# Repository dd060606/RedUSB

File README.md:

# RedUSB

RedUSB is a DIY USB macro device: a custom PCB built around an **Adafruit KB2040 (RP2040)** that acts as a programmable USB HID keyboard. You write simple scripts in a Ducky-Script–style language, drop them onto the device like a USB stick, and play them back as real keystrokes.

A single physical switch flips the device between two personalities:

- **Config mode** : the device appears as a USB flash drive. Copy your `.txt` scripts onto it.
- **Attack mode** : the device appears as a USB keyboard. The selected script runs automatically on connect (or on a button press).

The firmware is written in Rust (`no_std`) and runs bare-metal on the RP2040.

---

## Features

- **Ducky-Script–style language** : `STRING`, `DELAY`, `REPEAT`, key combos (`GUI r`, `CTRL ALT t`, ...), and more.
- **Up to 16 scripts on the device**, selectable with the button; an RGB LED shows which one is active.
- **Auto-run on connect** : in attack mode the selected script fires once the host is ready.
- **US / French (AZERTY) keyboard layouts**, switchable per script with `LAYOUT`.
- **Conditional execution** per host OS with `IF_OS` / `ELSE` / `END_IF` (best-effort detection).
- **Firmware updates over USB** (UF2), no external programmer required.

---

## How it works

The **mode switch** (GPIO8) selects the personality at power-up:

| Switch       | Mode       | USB device                    | Button does               |
| ------------ | ---------- | ----------------------------- | ------------------------- |
| To GND (low) | **Config** | Mass storage (`REDUSB` drive) | Cycle the selected script |
| Open (high)  | **Attack** | HID keyboard                  | Run the selected script   |

Flipping the switch while plugged in reboots the device into the other mode.

### Config mode

The device mounts as a FAT drive named `REDUSB`. Copy script files (`.txt`) onto it. Each button press selects the next script, and the LED shows its slot color so you know which one is armed. The selection is saved to flash and survives power cycles.

### Attack mode

The device enumerates as a USB keyboard. About a second after the host finishes setting it up, the **selected script runs automatically**. You can also press the button at any time to re-run it.

> **Safety:** because the script auto-runs on connect, make sure the right script is selected and the intended window is focused before you plug into attack mode. Only use this on machines you are authorized to test.

---

## Hardware

- **MCU board:** Adafruit KB2040 (RP2040, 8 MB QSPI flash)
- **Push button** on GPIO5 (active-low, to GND)
- **Mode switch** on GPIO8 (active-low, to GND)
- **RGB LED** (common anode, active-low): blue = GPIO2, red = GPIO3, green = GPIO4
- **USB-A** connector and a 500 mA resettable fuse on the PCB

KiCad sources, the 3D model, and production/assembly files live in `PCB/` and `3D/`.

---

## Repository layout

```
RedUSB/
├── 3D/            Mechanical / enclosure model
├── PCB/           KiCad project and fabrication files
├── Firmware/      Rust firmware (Cargo workspace)
│   ├── core/      Hardware-independent logic: FAT, Ducky engine, layouts (host-tested)
│   └── firmware/  RP2040 binary: USB, flash storage, LED, button, modes
├── scripts/       Ready-to-run test / example scripts
└── README.md
```

---

## Building and flashing

### Prerequisites

Install the [Rust toolchain](https://rustup.rs/) (the correct target is pinned by `rust-toolchain.toml`), then the two build/flash helpers:

```bash
cargo install flip-link      # linker used by the firmware
cargo install elf2uf2-rs     # builds the UF2 and copies it to the board
```

All firmware commands below are run from the `Firmware/firmware/` directory.

### Flashing

`cargo run --release` builds **and** flashes in a single step : the project's Cargo runner converts the firmware to a `.uf2` and copies it to the board, so there's no separate build command to remember.

1. Put the board into bootloader mode. It should appear as the `RPI-RP2` drive:
    - **First flash (blank board):** hold the **BOOT button on the KB2040 itself** while plugging in the USB cable.
    - **Updating an already-flashed board:** set the mode switch to **Config**, hold the **PCB button (GPIO5)**, then plug in : the firmware reboots straight into the bootloader.
2. Flash it:
    ```bash
    cargo run --release
    ```
    The board reboots into the new firmware when it finishes.

> To just compile without flashing (for example to check it builds), use `cargo build --release`.

---

## Writing and running scripts

Scripts are plain `.txt` files placed in the root of the `REDUSB` drive (config mode). Filenames follow the FAT **8.3** convention (up to 8 characters before the extension), and scripts are sorted by name, so prefixes like `1_`, `2_` give a predictable order. Up to 16 scripts are tracked.

See the [`scripts/`](scripts/) folder for ready-to-run examples that exercise every feature.

### Workflow

1. Set the switch to **Config** and plug in. The `REDUSB` drive appears.
2. Copy your `.txt` script(s) onto it.
3. Press the button to select a script (the LED color tells you which : see below).
4. Focus the target window, then set the switch to **Attack** and plug in. The selected script runs automatically (or press the button).

### Script language

| Command                     | Example                              | Meaning                                                        |
| --------------------------- | ------------------------------------ | -------------------------------------------------------------- |
| `REM`                       | `REM a comment`                      | Comment, ignored                                               |
| `STRING`                    | `STRING hello`                       | Type text (no newline)                                         |
| `STRINGLN`                  | `STRINGLN hello`                     | Type text, then Enter                                          |
| `DELAY`                     | `DELAY 500`                          | Wait 500 ms                                                    |
| `DEFAULT_DELAY`             | `DEFAULT_DELAY 50`                   | Pause after every command                                      |
| `REPEAT`                    | `REPEAT 3`                           | Repeat the previous command 3 more times                       |
| `LAYOUT`                    | `LAYOUT FR`                          | Keyboard layout for `STRING` (`US` or `FR`)                    |
| Key / combo                 | `GUI r`, `CTRL ALT t`, `ENTER`, `F5` | Press a key, optionally with modifiers                         |
| `IF_OS` … `ELSE` … `END_IF` | `IF_OS WINDOWS`                      | Run a block only on a given OS                                 |
| `OS_REPORT`                 | `OS_REPORT`                          | Type the detected OS and USB enumeration counters (diagnostic) |

Modifiers: `CTRL`, `SHIFT`, `ALT`, `GUI`/`WINDOWS`, `ALTGR`. The default layout is French (AZERTY).

---

## LED reference

**Config mode : selected script slot:**

| Slot  | 0   | 1     | 2    | 3      | 4    | 5       | 6     | 7      |
| ----- | --- | ----- | ---- | ------ | ---- | ------- | ----- | ------ |
| Color | Red | Green | Blue | Yellow | Cyan | Magenta | White | Orange |

(Slots 8–15 use the same colors, blinking. A slow white "breathing" glow means no scripts are present.)

**Attack mode:**

| LED                     | Meaning                                        |
| ----------------------- | ---------------------------------------------- |
| Dim selected-slot color | Idle, ready                                    |
| Solid white             | Script running                                 |
| Red flash (1.5 s)       | No script to run                               |
| Magenta flash           | Keystroke timed out (host not accepting input) |
| Orange flash            | Script line could not be parsed                |
| Yellow flash            | Script file could not be read from flash       |
| Cyan flash              | Malformed `IF_OS` / `ELSE` / `END_IF`          |

---

## Debugging

For everyday use the LED is enough. For detailed logs, the firmware emits [`defmt`](https://defmt.ferrous-systems.com/) over RTT, which needs an SWD debug probe (for example a second Raspberry Pi Pico flashed as a debug probe) wired to the KB2040's SWD pads:

```bash
cargo install probe-rs-tools
probe-rs attach --chip RP2040 target/thumbv6m-none-eabi/release/firmware
```

Host-side logic in `core/` is unit-tested:

```bash
cd Firmware/core && cargo test
```

---

## License

MIT © dd060606

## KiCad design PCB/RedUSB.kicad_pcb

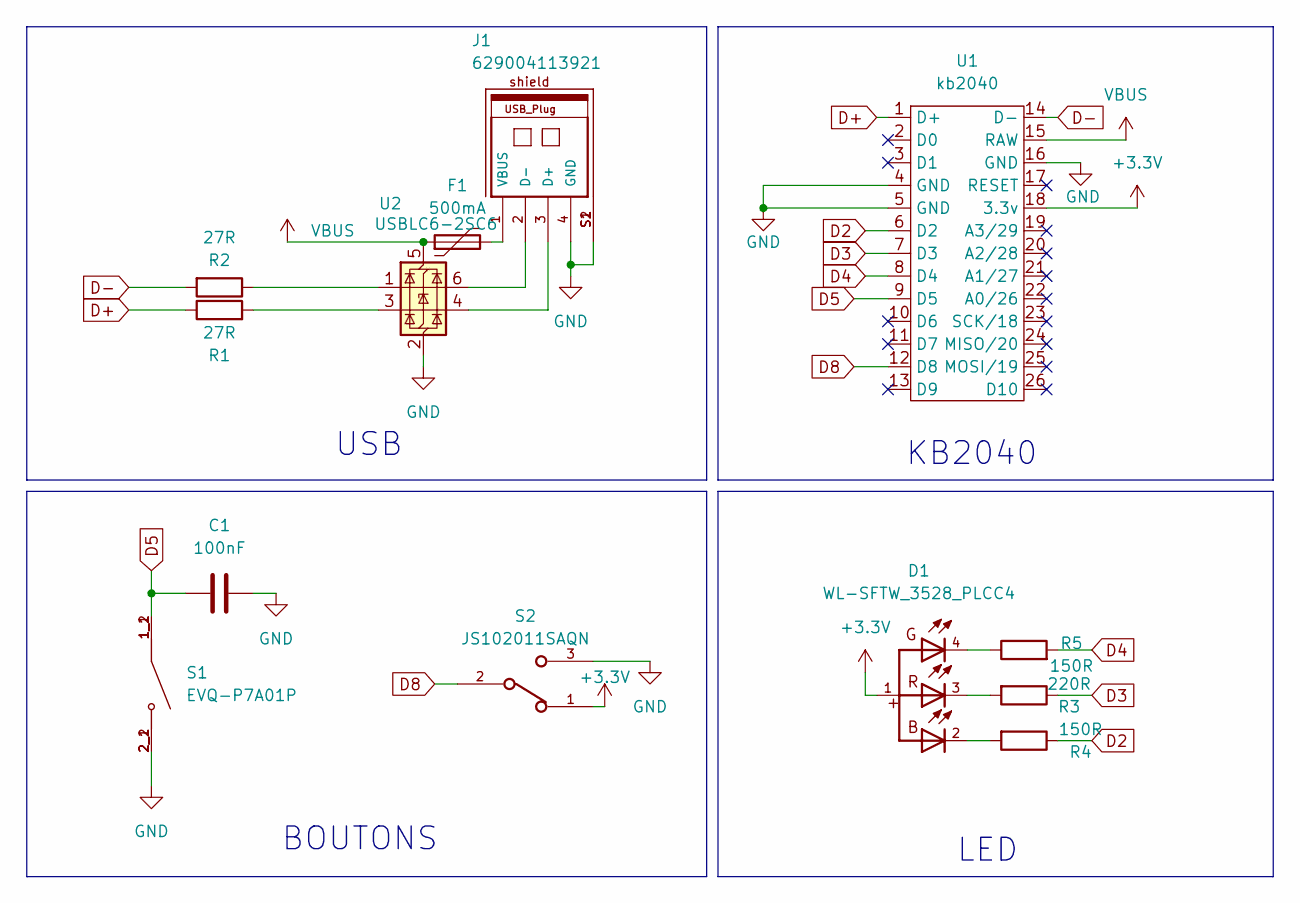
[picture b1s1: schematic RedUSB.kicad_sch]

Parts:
C1: 100nF; C_0603_1608Metric_Pad1.08x0.95mm_HandSolder
D1: WL-SFTW_3528_PLCC4; LED_RGB_Wuerth-PLCC4_3.2x2.8mm_150141M173100
F1: 500mA; Fuse_0805_2012Metric_Pad1.15x1.40mm_HandSolder
J1: 629004113921
R1, R2: 27R; R_0603_1608Metric_Pad0.98x0.95mm_HandSolder
R3: 220R; R_0603_1608Metric_Pad0.98x0.95mm_HandSolder
R4, R5: 150R; R_0603_1608Metric_Pad0.98x0.95mm_HandSolder
S1: EVQ-P7A01P; SW_EVQ-P7A01P; PARTREV 2022.4
S2: JS102011SAQN; SW_JS102011SAQN
U1: kb2040
U2: USBLC6-2SC6; SOT-23-6_Handsoldering

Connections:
+3.3V: D1.1, S2.1, U1.18 (3.3v)
D2: R4.1, U1.6 (D2)
D3: R3.1, U1.7 (D3)
D4: R5.2, U1.8 (D4)
D5: C1.1, S1.1_1, S1.1_2, U1.9 (D5)
D8: S2.2, U1.12 (D8)
D+: R1.1, U1.1 (D+)
D-: R2.2, U1.14 (D-)
GND: C1.2, J1.4 (GND), J1.S1, J1.S2, S1.2_1, S1.2_2, S2.3, U1.4 (GND), U1.5 (GND), U1.16 (GND), U2.2 (GND)
unnamed: D1.2, R4.2
unnamed: D1.3, R3.2
unnamed: D1.4, R5.1
unnamed: J1.3 (D+), U2.4 (I/O2)
unnamed: J1.2 (D-), U2.6 (I/O1)
unnamed: F1.2, J1.1 (VBUS)
unnamed: R1.2, U2.3 (I/O2)
unnamed: R2.1, U2.1 (I/O1)
VBUS: F1.1, U1.15 (RAW), U2.5 (VBUS)

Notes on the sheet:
KB2040
BOUTONS
USB
LED

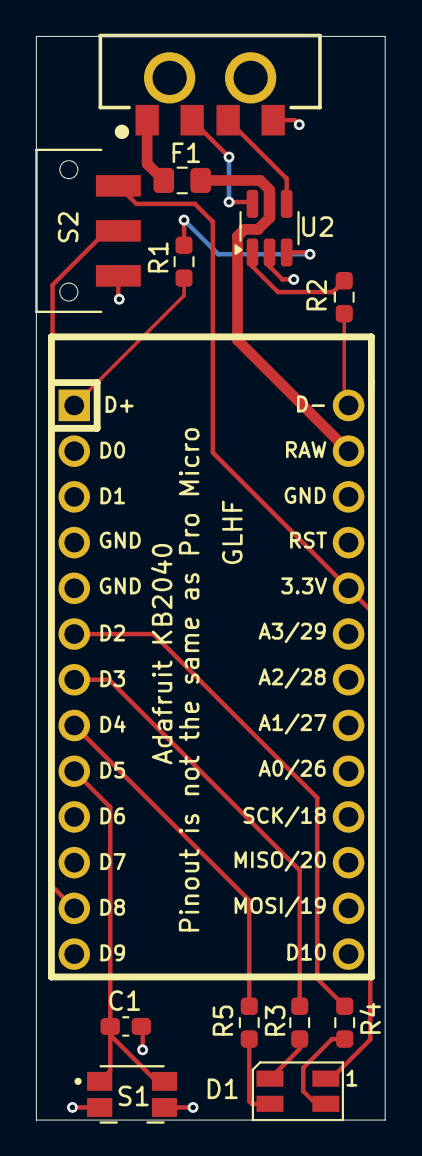
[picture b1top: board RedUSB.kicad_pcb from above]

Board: 2 copper layers, 19.4 x 60.2 mm, 13 parts (0 on the bottom side), 18 nets.

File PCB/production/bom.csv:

Designator,Footprint,Quantity,Value,LCSC Part #
C1,0603,1,100nF,
D1,LED_RGB_Wuerth-PLCC4_3.2x2.8mm_150141M173100,1,WL-SFTW_3528_PLCC4,
F1,0805,1,500mA,
J1,629004113921,1,629004113921,
"R1, R2",0603,2,27R,
R3,0603,1,220R,
"R4, R5",0603,2,150R,
S1,SW_EVQ-P7A01P,1,EVQ-P7A01P,
S2,SW_JS102011SAQN,1,JS102011SAQN,
U1,kb2040,1,kb2040,
U2,SOT-23-6_Handsoldering,1,USBLC6-2SC6,
